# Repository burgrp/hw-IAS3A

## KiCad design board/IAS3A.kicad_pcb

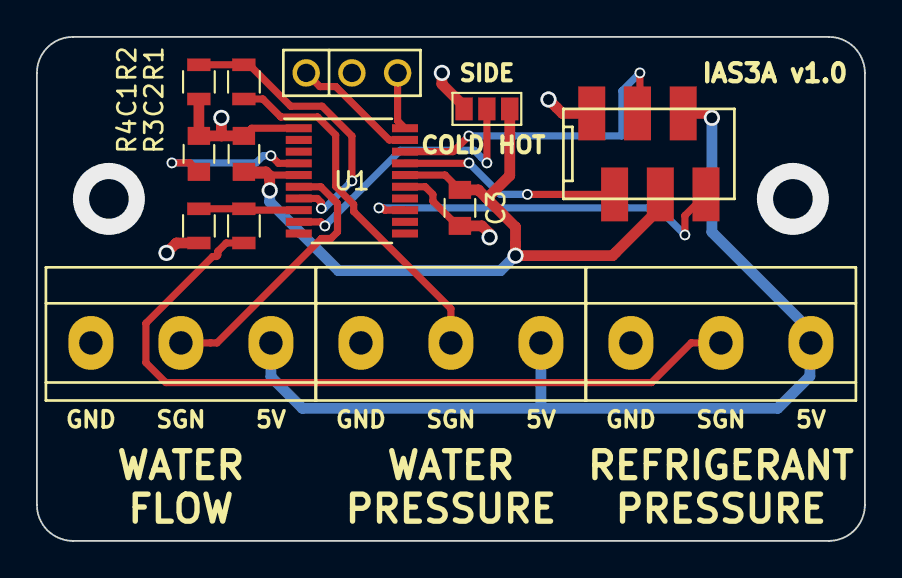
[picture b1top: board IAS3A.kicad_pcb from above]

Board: 2 copper layers, 46.0 x 28.0 mm, 14 parts (0 on the bottom side), 15 nets.

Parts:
C1, C2, C3: 100n; C_0805
J1: Address; GS3
J2: Flow Ext; DG301-5.0-03
J3: Pressure Ext; DG301-5.0-03
J4: Pressure Int; DG301-5.0-03
R1, R3: 4k7; R_0805
R2, R4: 10k; R_0805
U1: STM32F030F4Px; TSSOP-20_4.4x6.5mm_Pitch0.65mm
X1: I2C-6P; Micro-Match-FOB-6
X2: SWD

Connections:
+3V3: C2.1, C3.1, J1.3, U1.5, U1.16, X1.4
+5V: J2.3, J3.3, J4.3, X1.5
/ALERT: U1.13, X1.6
/SCL: U1.17, X1.2
/SDA: U1.18, X1.3
/SWCLK: U1.20, X2.3
/SWDIO: U1.19, X2.1
GND: C1.2, C2.2, C3.2, J1.1, J2.1, J3.1, J4.1, R2.1, R4.1, U1.1, U1.15, X1.1, X2.2
unnamed: C1.1, U1.4
unnamed: J1.2, U1.9
unnamed: J2.2, U1.6
unnamed: J3.2, R1.1
unnamed: J4.2, R3.1
unnamed: R1.2, R2.2, U1.7
unnamed: R3.2, R4.2, U1.8
